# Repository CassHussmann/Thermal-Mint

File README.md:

# Thermal-Mint
ESP32 based temperature logger / controller

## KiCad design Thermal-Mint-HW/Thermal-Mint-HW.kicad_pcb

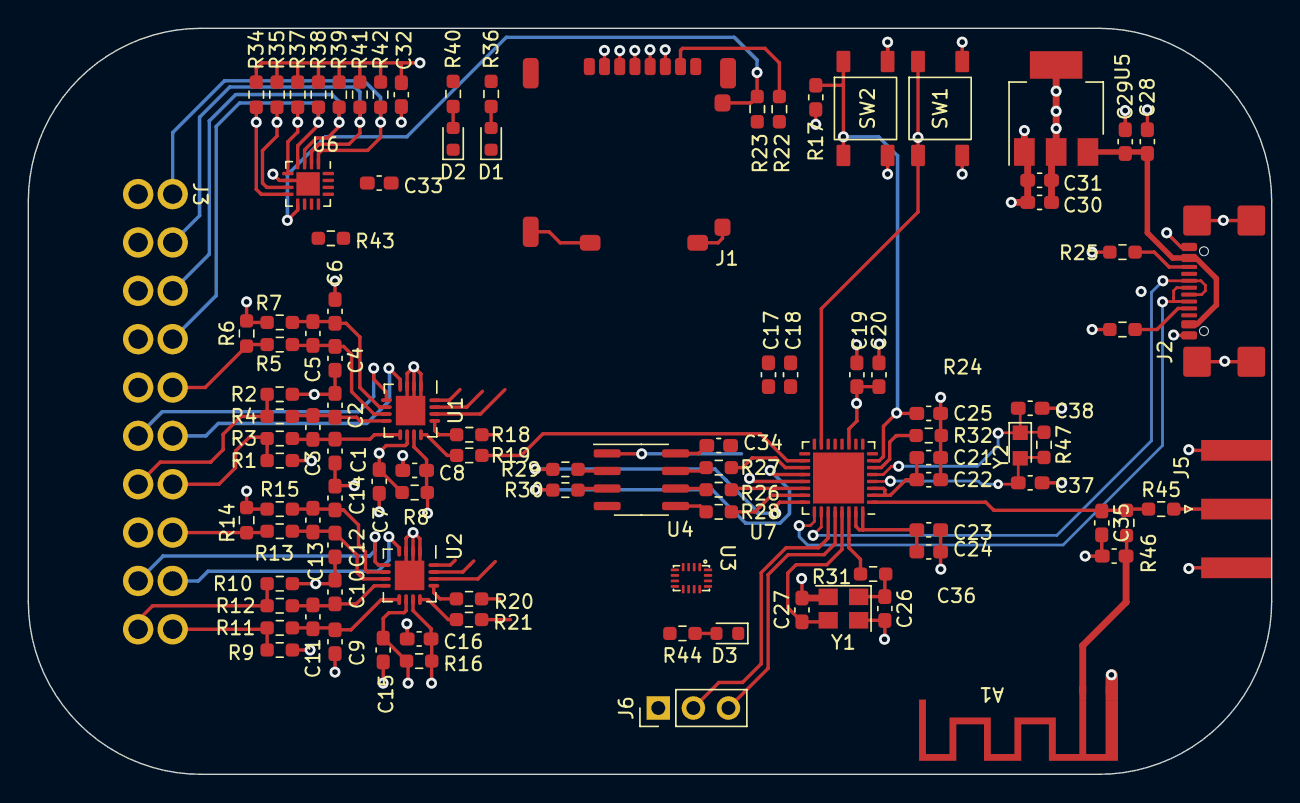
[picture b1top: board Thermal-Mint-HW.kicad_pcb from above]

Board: 4 copper layers, 90.0 x 54.0 mm, 104 parts (0 on the bottom side), 83 nets.

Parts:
A1: AntennaWithGround; WifiAntenna
C1, C2, C4, C6, C9, C10, C12, C14: 10n; C_0603_1608Metric_Pad1.08x0.95mm_HandSolder
C3, C5, C7, C8, C11, C13, C15, C16, C17, C18, C19, C20, C21, C22, C23, C24, C25, C28, C29, C30, C31, C32, C33, C34: 470n; C_0603_1608Metric_Pad1.08x0.95mm_HandSolder
C26, C27: 15p; C_0603_1608Metric_Pad1.08x0.95mm_HandSolder
C35, C37, C38: DNF; C_0603_1608Metric_Pad1.08x0.95mm_HandSolder
C36: 1p; C_0603_1608Metric_Pad1.08x0.95mm_HandSolder
D1, D2, D3: LED; LED_0603_1608Metric
J1: Molex_5031821852; Molex_SDCard_5031821852
J2: USB4110-GF-A
J3: Conn_01x20_Male; 1786918_02_DMC
J5: Conn_Coaxial; SMA_Amphenol_132289_EdgeMount
J6: Conn_01x03_Female; PinHeader_1x03_P2.54mm_Vertical
R1, R2, R9, R10, R45, R47: DNF; R_0603_1608Metric_Pad0.98x0.95mm_HandSolder
R3, R4, R5, R7, R11, R12, R13, R15: 820; R_0603_1608Metric_Pad0.98x0.95mm_HandSolder
R6, R14: 1.65k; R_0603_1608Metric_Pad0.98x0.95mm_HandSolder
R8, R16: 10; R_0603_1608Metric_Pad0.98x0.95mm_HandSolder
R17: 10k; R_0603_1608Metric_Pad1.05x0.95mm_HandSolder
R18, R19, R20, R21, R22, R26, R27, R28, R29, R30, R43: 24; R_0603_1608Metric_Pad0.98x0.95mm_HandSolder
R23, R32: 10k; R_0603_1608Metric_Pad0.98x0.95mm_HandSolder
R24, R25: 5.1k; R_0603_1608Metric_Pad0.98x0.95mm_HandSolder
R31, R46: 0; R_0603_1608Metric_Pad0.98x0.95mm_HandSolder
R34, R35, R36, R37, R38, R39, R40, R41, R42, R44: 1k; R_0603_1608Metric_Pad0.98x0.95mm_HandSolder
SW1, SW2: PTS647; SW_SPST_PTS647
U1, U2: ADS1220-VQFN; QFN-16_EP_3.5x3.5_Pitch0.5mm
U3: SN74LVC138ARSVR; UQFN16 - RSV0016A
U4: AT25DL081-SSHN-T; SOIC-8_3.9x4.9mm_P1.27mm
U5: NCP1117-3.3_SOT223; SOT-223-3_TabPin2
U6: MAX7317ATE+; QFN-16-1EP_3x3mm_P0.5mm_EP1.7x1.7mm
U7: ESP32-C3; QFN-32-1EP_5x5mm_P0.5mm_EP3.7x3.7mm
Y1: FL4000157Z; Crystal_SMD_3225-4Pin_3.2x2.5mm
Y2: CM8V-T1A-32.768KHZ-12.5PF-20PPM-TA-QA; Crystal_SMD_TXC_9HT11-2Pin_2.0x1.2mm_HandSoldering

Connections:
+3V3: C8.1, C16.1, C17.1, C18.1, C19.1, C20.1, C21.1, C22.1, C23.1, C24.1, C30.1, C31.1, C33.1, C34.1, J1.4 (VDD), R8.2, R16.2, R17.1, R23.1, R36.2, R40.2, R44.2, U1.11 (DVDD), U2.11 (DVDD), U3.6 (G1), U3.16 (Vcc), U4.8 (VCC), U5.2 (VO), U6.14 (V+), U7.2 (VDD3P3), U7.3 (VDD3P3), U7.11 (VDD3P3_RTC), U7.17 (VDD3P3_CPU), U7.31 (VDDA), U7.32 (VDDA)
+5V: C28.1, C29.1, C32.1, J2.A4 (VBUS), J2.A9 (VBUS), J2.B4 (VBUS), J2.B9 (VBUS), R34.2, R35.2, R37.2, R38.2, R39.2, R41.2, R42.2, U5.3 (VI)
/ADC1AIN0: J3.7, R1.2, R3.1
/ADC1AIN1: J3.17, R2.1, R4.1
/ADC1AIN2: J3.16, U1.5 (AIN2)
/ADC1AIN3: J3.6, U1.4 (AIN3/REFN1)
/ADC1REFIN: J3.5, R5.1, R6.1
/ADC2AIN0: J3.10, R9.2, R11.1
/ADC2AIN1: J3.20, R10.1, R12.1
/ADC2AIN2: J3.19, U2.5 (AIN2)
/ADC2AIN3: J3.9, U2.4 (AIN3/REFN1)
/ADC2REFIN: J3.8, R13.1, R14.1
/ADS1220_1/AVDD: C7.1, R1.1, R8.1, U1.10 (AVDD)
/ADS1220_2/AVDD: C15.1, R9.1, R16.1, U2.10 (AVDD)
/CS1: U1.16 (nCS), U3.14 (Y1)
/CS2: U2.16 (nCS), U3.13 (Y2)
/CS3: J1.2 (DAT3/CD), U3.12 (Y3)
/CS4: U3.11 (Y4), U6.16 (~CS)
/DIN: R18.2, R20.2, R22.2, R43.2, U7.13 (GPIO7)
/DOUT: J1.3 (CMD), U1.14 (DIN), U2.14 (DIN), U6.13 (DIN), U7.16 (GPIO10)
/GPIO0: J3.1, R42.1, U6.1 (P0)
/GPIO1: J3.2, R41.1, U6.2 (P1)
/GPIO2: J3.3, R39.1, U6.3 (P2)
/GPIO3: J3.4, R38.1, U6.4 (P3)
/GPIO4: R37.1, U6.5 (P4)
/GPIO5: R35.1, U6.7 (P5)
/GPIO6: R34.1, U6.8 (P6)
/GPIO7: J1.9 (SW), R23.2, U6.9 (P7)
/SCLK: J1.5 (CLK), U1.15 (SCLK), U2.15 (SCLK), U6.15 (SCLK), U7.12 (GPIO6)
/TM-ESP32/D+: J2.A6 (D+), J2.B6 (D+), U7.26 (USB_D+)
/TM-ESP32/D-: J2.A7 (D-), J2.B7 (D-), U7.25 (USB_D-)
/TM-ESP32/DecoderA0: U3.3 (C), U7.8 (GPIO3)
/TM-ESP32/DecoderA1: U3.2 (B), U7.9 (GPIO4)
/TM-ESP32/DecoderA2: U3.1 (A), U7.10 (GPIO5)
/TM-ESP32/RF: C35.1, R45.1, R46.1, U7.1 (LNA_IN)
/TM-ESP32/RXD: J6.2, U7.27 (U0RXD)
/TM-ESP32/SPICLK: R26.1, U7.22 (SPICLK)
/TM-ESP32/SPICS0: U4.1 (/CS), U7.21 (SPICS0)
/TM-ESP32/SPID: R28.2, U7.23 (SPID)
/TM-ESP32/SPIHD: R27.1, U7.19 (SPIHD)
/TM-ESP32/SPIQ: R29.2, U7.24 (SPIQ)
/TM-ESP32/SPIWP: R30.2, U7.20 (SPIWP)
/TM-ESP32/TXD: J6.3, U7.28 (U0TXD)
/TM-ESP32/XTAL_32k_N: C38.1, R47.1, U7.5 (XTAL_32K_N), Y2.1
/TM-ESP32/XTAL_32k_P: C37.1, R47.2, U7.4 (XTAL_32K_P), Y2.2
/TM-ESP32/XTAL_N: C27.1, U7.29 (XTAL_N), Y1.3
/TM-ESP32/XTAL_P: C26.1, R31.2, Y1.1
/nDRDY1: R19.2, U7.18 (GPIO11)
/nDRDY2: R21.2, U7.14 (GPIO8)
GND: A1.2 (GND), C1.1, C2.2, C4.2, C6.1, C7.2, C8.2, C9.1, C10.2, C12.2, C14.1, C15.2, C16.2, C17.2, C18.2, C19.2, C20.2, C21.2, C22.2, C23.2, C24.2, C25.2, C26.2, C27.2, C28.2, C29.2, C30.2, C31.2, C32.2, C33.2, C34.2, C35.2, C36.2, C37.2, C38.2, J1.6 (VSS), J1.10 (SW_Shield), J1.11 (Shield), J1.12 (Shield), J1.13 (Shield), J1.14 (Shield), J1.15 (Shield), J2.A1 (GND), J2.A12 (GND), J2.B1 (GND), J2.B12 (GND), J2.S1 (SHIELD), J3.11, J3.12, J3.13, J3.14, J3.15, J3.18, J5.2 (Ext), J6.1, R2.2, R6.2, R7.1, R10.2, R14.2, R15.1, R24.1, R25.1, R32.2, SW1.3, SW1.4, SW2.3, SW2.4, U1.1 (CLK), U1.2 (DGND), U1.3 (AVSS), U1.17 (EP), U2.1 (CLK), U2.2 (DGND), U2.3 (AVSS), U2.17 (EP), U3.4 (~G2A), U3.5 (~G2B), U3.8 (GND), U4.4 (GND), U5.1 (GND), U6.6 (GND), U6.17 (EP), U7.33 (GND), Y1.2, Y1.4
unnamed: A1.1 (A), C36.1, R46.2
unnamed: D1.2 (A), R36.1
unnamed: D1.1 (K), U6.11 (P9)
unnamed: D2.2 (A), R40.1
unnamed: D2.1 (K), U6.10 (P8)
unnamed: D3.2 (A), R44.1
unnamed: D3.1 (K), U3.15 (Y0)
unnamed: J1.7 (DAT0), R22.1
unnamed: J2.A5 (CC1), R24.2
unnamed: J2.B5 (CC2), R25.2
unnamed: J5.1 (In), R45.2
unnamed: C1.2, C3.1, R3.2, U1.9 (AIN0/REFP1)
unnamed: C2.1, C3.2, R4.2, U1.8 (AIN1)
unnamed: R18.1, U1.13 (DOUT/nDRDY)
unnamed: C5.1, C6.2, R7.2, U1.6 (REFN0)
unnamed: C4.1, C5.2, R5.2, U1.7 (REFP0)
unnamed: R19.1, U1.12 (nDRDY)
unnamed: C9.2, C11.1, R11.2, U2.9 (AIN0/REFP1)
unnamed: C10.1, C11.2, R12.2, U2.8 (AIN1)
unnamed: R20.1, U2.13 (DOUT/nDRDY)
unnamed: C13.1, C14.2, R15.2, U2.6 (REFN0)
unnamed: C12.1, C13.2, R13.2, U2.7 (REFP0)
unnamed: R21.1, U2.12 (nDRDY)
unnamed: R26.2, U4.6 (CLK)
unnamed: R28.1, U4.5 (DI)
unnamed: R29.1, U4.2 (DO)
unnamed: R27.2, U4.7 (/HOLD)
unnamed: R30.1, U4.3 (/WP)
unnamed: R43.1, U6.12 (Dout)
unnamed: C25.1, R17.2, SW2.1, SW2.2, U7.7 (CHIP_EN)
unnamed: R32.1, U7.6 (GPIO2)
unnamed: SW1.1, SW1.2, U7.15 (GPIO9)
unnamed: R31.1, U7.30 (XTAL_P)

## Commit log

2021-09-14 Initial project setup
2021-09-14 Moving libraries to local
2022-03-09 WIP commit, Adding connectors and memory
2022-03-29 Clean up of output circuits
2022-04-02 Cleanup of Rev1 schematics for review
2023-03-06 Temporary commit before changing processor from C3 to s2
2023-03-06 Schematic update to ESP32-S2
    Updated schematic from ESP32-C3 to the S2 chips with more pins, allowed the removal of the GPO expander and CS mux as well as addition of JTAG
2023-03-07 Adding a pdf of the new schematics
